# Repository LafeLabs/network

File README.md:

# [The Network](https://github.com/LafeLabs/network)

*everything replicates!*

 - [index.html](index.html)
 - [MUSIC/](music/)
 - [STONE SOUP/](stonesoup/)
 - [BRACKETS/](brackets/)
 - [TERMINAL/](terminal/)
 - [PODCASTS/](podcasts/)
 - [BOOKS/](books/)
 - [ZINES/](zines/)
 - [Fashion/](fashion/)
 - [Freestore/](freestore/)
 - [Laws of the Network/](laws/)
 - [DIRT PIPE/](dirtpipe/)
 - [INTERNET OF SQUARES/](squares/)
 - [write on the wall](wall.html)
 - [page/](page/)
 - [QR Code](qrcode.html)
 - [STREET NETWORK/](street/)
 - [WATERSHED NETWORK](watershed/)
 - [WHAT CAN I DO FOR THE NETWORK?/](network-actions/)
 - [WHAT CAN THE NETWORK DO FOR ME?](network-benefits/)
 - [fork.html](fork.html)

1. Get a 8 foot 1x4.
2. Cut off two sections each 24 inches long
3. Cut off a section 28 inches long
4. print out the screen bracket
5. print out the board bracket
6. print out 4 of the flat bracket
6. print out the pi bracket and add M2.5 thread inserts
7. print out the circuit playground bracket and add 4-40 thread inserts
8. drill all the holes in all the boards
9. assemble all the screws

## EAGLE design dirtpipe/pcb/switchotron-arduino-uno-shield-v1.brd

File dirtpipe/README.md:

## [Up A Level](../)

# [DIRT PIPE](https://github.com/LafeLabs/network/tree/main/dirtpipe)

## RITUAL THE FIRST

GET DIRT PIPE FROM A MAKER, TEST IT OUT, PLAY THE BUTTONS AND THE KNOBS

## RITUAL THE SECOND

INSTALL THE [ARDUINO IDE](https://www.arduino.cc/en/software)

INSTALL THE MOZZI LIBRARY

INSTALL THE ADAFRUIT NEOPIXEL LIBRARY

COPY/PASTE THE CODE FROM THE BOTTOM OF THIS DOCUMENT INTO THE ARDUINO IDE, BEING SURE TO TOTALLY REPLACE THE DEFAULT CODE RATHER THAN ADD TO IT

CHECK THE CODE BY CLICKING THE CHECK BOX

UPLOAD THE CODE

RE-TEST THE DIRT PIPE

## RITUAL THE THIRD

CHANGE THE DIRT PIPE TO PLAY A TONE AT SOME FIXED FREQUENCY

CHANGE THE COLORS OF THE BUTTONS

CREATE YOUR OWN THING AND SHARE IT WITH THE WORLD

[link to the circuit boards on pcbway.com](https://www.pcbway.com/project/shareproject/W224521BSI51_dirtpipe_UNO_shield_v1_2024_04_04_8aeaeaa8.html)

[digikey cart with all the parts other than headers](https://www.digikey.com/short/bcr3z21v)

[headers on amazon](https://www.amazon.com/Header-Lystaii-Pin-Connector-Electronic/dp/B06ZZN8L9S/)

## 1/2 inch #4 wood screws

## 4-40 Screws for Arduino UNO and Circuit Playground Express

## 4-40 Thread Inserts

## Thread insert tool 

## AnkerMake 3d printer

```
#include <Adafruit_NeoPixel.h>
#ifdef __AVR__
#endif

// Which pin on the Arduino is connected to the NeoPixels?
#define PIN 12 // On Trinket or Gemma, suggest changing this to 1

// How many NeoPixels are attached to the Arduino?
#define NUMPIXELS 8 // 
//there are 8

// When setting up the NeoPixel library, we tell it how many pixels,  
// and which pin to use to send signals. Note that for older NeoPixel
// strips you might need to change the third parameter -- see the
// strandtest example for more information on possible values.
Adafruit_NeoPixel pixels(NUMPIXELS, PIN, NEO_GRB + NEO_KHZ800);

int buttons0 = 0;
int buttons1 = 0;
int buttons0_2 = 0;
int buttons1_2 = 0;
int buttonmode0 = 0;
int buttonmode1 = 0;

int modevoltage1 = 110;
int modevoltage2 = 215;
int modevoltage3 = 320;
int modevoltage4 = 425;
int modevoltage5 = 542;
int modevoltage6 = 670;
int modevoltage7 = 820;

int delta =  20;

int knob = 0;
boolean on = false;
boolean test = false;

#include <MozziGuts.h>
#include <Oscil.h> // oscillator template
#include <tables/sin2048_int8.h> // sine table for oscillator

// use: Oscil <table_size, update_rate> oscilName (wavetable), look in .h file of table #included above
Oscil <SIN2048_NUM_CELLS, AUDIO_RATE> aSin(SIN2048_DATA);

// use #define for CONTROL_RATE, not a constant
#define CONTROL_RATE 64 // Hz, powers of 2 are most reliable

void setup() {
    Serial.begin(115200);
    knob = analogRead(A3);
    buttons0 = analogRead(A0);
    buttons1 = analogRead(A1);
    pinMode(15,INPUT_PULLUP);
    pinMode(16,INPUT_PULLUP);
    pixels.begin(); // INITIALIZE NeoPixel strip object (REQUIRED)
    startMozzi(CONTROL_RATE); // :)
    aSin.setFreq(2600); // set the freq to knob in Hz
    pinMode(9,OUTPUT); 

}
void updateControl(){
  // put changing controls in here
}

AudioOutput_t updateAudio(){
  return MonoOutput::from8Bit(aSin.next()); // return an int signal centred around 0
}

void loop() {

  buttons0 = analogRead(A0);
  buttons1 = analogRead(A4);
  //delay(30);
  buttons0_2 = analogRead(A0);
  buttons1_2 = analogRead(A4);

  knob = analogRead(A3);
  on = !digitalRead(15);
  test = !digitalRead(16);

  if(buttons0 <  delta && buttons0_2 < delta){
    buttonmode0 = 0;
  }
  if(buttons0 > modevoltage1 - delta && buttons0 < modevoltage1 + delta && buttons0_2 > modevoltage1 - delta && buttons0_2 < modevoltage1 + delta){
    buttonmode0 = 1;
  }
  if(buttons0 > modevoltage2 - delta && buttons0 < modevoltage2 + delta && buttons0_2 > modevoltage2 - delta && buttons0_2 < modevoltage2 + delta){
    buttonmode0 = 2;
  }
  if(buttons0 > modevoltage3 - delta && buttons0 < modevoltage3 + delta && buttons0_2 > modevoltage3 - delta && buttons0_2 < modevoltage3 + delta){
    buttonmode0 = 3;
  }
  if(buttons0 > modevoltage4 - delta && buttons0 < modevoltage4 + delta && buttons0_2 > modevoltage4 - delta && buttons0_2 < modevoltage4 + delta){
    buttonmode0 = 4;
  }
  if(buttons0 > modevoltage5 - delta && buttons0 < modevoltage5 + delta && buttons0_2 > modevoltage5 - delta && buttons0_2 < modevoltage5 + delta){
    buttonmode0 = 5;
  }
  if(buttons0 > modevoltage6 - delta && buttons0 < modevoltage6 + delta && buttons0_2 > modevoltage6 - delta && buttons0_2 < modevoltage6 + delta){
    buttonmode0 = 6;
  }
  if(buttons0 > modevoltage7 - delta && buttons0 < modevoltage7 + delta && buttons0_2 > modevoltage7 - delta && buttons0_2 < modevoltage7 + delta){
    buttonmode0 = 7;
  }
  if(buttons0 > 1024 - delta && buttons0_2 > 1024 - delta){
    buttonmode0 = 8;
  }

  if(buttons1 <  delta && buttons1_2 < delta){
    buttonmode1 = 0;
  }
  if(buttons1 > modevoltage1 - delta && buttons1 < modevoltage1 + delta && buttons1_2 > modevoltage1 - delta && buttons1_2 < modevoltage1 + delta){
    buttonmode1 = 1;
  }
  if(buttons1 > modevoltage2 - delta && buttons1 < modevoltage2 + delta && buttons1_2 > modevoltage2 - delta && buttons1_2 < modevoltage2 + delta){
    buttonmode1 = 2;
  }
  if(buttons1 > modevoltage3 - delta && buttons1 < modevoltage3 + delta && buttons1_2 > modevoltage3 - delta && buttons1_2 < modevoltage3 + delta){
    buttonmode1 = 3;
  }
  if(buttons1 > modevoltage4 - delta && buttons1 < modevoltage4 + delta && buttons1_2 > modevoltage4 - delta && buttons1_2 < modevoltage4 + delta){
    buttonmode1 = 4;
  }
  if(buttons1 > modevoltage5 - delta && buttons1 < modevoltage5 + delta && buttons1_2 > modevoltage5 - delta && buttons1_2 < modevoltage5 + delta){
    buttonmode1 = 5;
  }
  if(buttons1 > modevoltage6 - delta && buttons1 < modevoltage6 + delta && buttons1_2 > modevoltage6 - delta && buttons1_2 < modevoltage6 + delta){
    buttonmode1 = 6;
  }
  if(buttons1 > modevoltage7 - delta && buttons1 < modevoltage7 + delta && buttons1_2 > modevoltage7 - delta && buttons1_2 < modevoltage7 + delta){
    buttonmode1 = 7;
  }
  if(buttons1 > 1024 - delta && buttons1_2 > 1024 - delta){
    buttonmode1 = 8;
  }

   if(buttonmode0 == 0 && buttonmode1 == 0){
    pixels.setPixelColor(0, pixels.Color(0, 0, 0));    
    pixels.setPixelColor(1, pixels.Color(0, 0, 0));    
    pixels.setPixelColor(2, pixels.Color(0, 0, 0));    
    pixels.setPixelColor(3, pixels.Color(0, 0, 0));    
    pixels.setPixelColor(4, pixels.Color(0, 0, 0));    
    pixels.setPixelColor(5, pixels.Color(0, 0, 0));    
    pixels.setPixelColor(6, pixels.Color(0, 0, 0));    
    pixels.setPixelColor(7, pixels.Color(0, 0, 0));     
   }
   if(buttonmode0 !=0 && buttonmode0 == buttonmode1){
    pixels.setPixelColor(0, pixels.Color(0, 0, 0));    
    pixels.setPixelColor(1, pixels.Color(0, 0, 0));    
    pixels.setPixelColor(2, pixels.Color(0, 0, 0));    
    pixels.setPixelColor(3, pixels.Color(0, 0, 0));    
    pixels.setPixelColor(4, pixels.Color(0, 0, 0));    
    pixels.setPixelColor(5, pixels.Color(0, 0, 0));    
    pixels.setPixelColor(6, pixels.Color(0, 0, 0));    
    pixels.setPixelColor(7, pixels.Color(0, 0, 0));     
    pixels.setPixelColor(buttonmode0 - 1, pixels.Color(200, 0, 200));        //purple
   }
   if(buttonmode0 !=0 && buttonmode0 != buttonmode1){
    pixels.setPixelColor(0, pixels.Color(0, 0, 0));    
    pixels.setPixelColor(1, pixels.Color(0, 0, 0));    
    pixels.setPixelColor(2, pixels.Color(0, 0, 0));    
    pixels.setPixelColor(3, pixels.Color(0, 0, 0));    
    pixels.setPixelColor(4, pixels.Color(0, 0, 0));    
    pixels.setPixelColor(5, pixels.Color(0, 0, 0));    
    pixels.setPixelColor(6, pixels.Color(0, 0, 0));    
    pixels.setPixelColor(7, pixels.Color(0, 0, 0));     
    pixels.setPixelColor(buttonmode0 - 1, pixels.Color(200, 0,0));        //red
    pixels.setPixelColor(buttonmode1 - 1, pixels.Color(0, 0,200));        //blue

   }
   if(buttonmode0 !=0 && buttonmode1 == 0){
    pixels.setPixelColor(0, pixels.Color(0, 0, 0));    
    pixels.setPixelColor(1, pixels.Color(0, 0, 0));    
    pixels.setPixelColor(2, pixels.Color(0, 0, 0));    
    pixels.setPixelColor(3, pixels.Color(0, 0, 0));    
    pixels.setPixelColor(4, pixels.Color(0, 0, 0));    
    pixels.setPixelColor(5, pixels.Color(0, 0, 0));    
    pixels.setPixelColor(6, pixels.Color(0, 0, 0));    
    pixels.setPixelColor(7, pixels.Color(0, 0, 0));     
    pixels.setPixelColor(buttonmode0 - 1, pixels.Color(200, 0,0));        //red

   }

   if(buttonmode1 !=0 && buttonmode0 == 0){
    pixels.setPixelColor(0, pixels.Color(0, 0, 0));    
    pixels.setPixelColor(1, pixels.Color(0, 0, 0));    
    pixels.setPixelColor(2, pixels.Color(0, 0, 0));    
    pixels.setPixelColor(3, pixels.Color(0, 0, 0));    
    pixels.setPixelColor(4, pixels.Color(0, 0, 0));    
    pixels.setPixelColor(5, pixels.Color(0, 0, 0));    
    pixels.setPixelColor(6, pixels.Color(0, 0, 0));    
    pixels.setPixelColor(7, pixels.Color(0, 0, 0));     
    pixels.setPixelColor(buttonmode1 - 1, pixels.Color(0, 0,200));        //blue

   }

  pixels.show();   // Send the updated pixel colors to the hardware.

  aSin.setFreq((buttonmode0+1)*knob);      

/*
  if(on){
  }
  if(!on && !test){
    aSin.setFreq(0);      

  }

*/

audioHook(); // required here

//Serial.println(buttons0);

//Serial.println(buttonmode1);

/*  
  Serial.print(buttons0); 
  Serial.print(",");   
  Serial.print(buttons1); 
  Serial.print(",");   
  Serial.println(knob); 

  if(on){
    Serial.println("ON");
  }
  if(test){
    Serial.println("TEST");
  }
  if(!on && !test){
    Serial.println("OFF");
  }
*/
  
}
```

## DIRT PIPE REPLICATOR CODE:

```
sudo wget https://raw.githubusercontent.com/LafeLabs/network/main/dirtpipe/replicator.sh -O replicator.sh
sudo sh replicator.sh
```

## LINKS

 - [editor.php](editor.php)
 - [webeditor.html](webeditor.html)
 - [localhost](http://localhost)
 - [write on the wall](wall.html)
 - [DIRT WIZARD ON TIKTOK](https://www.tiktok.com/@dirt_wizard666)
 - [DIRT WIZARD ON CYBERPUNK.LOL](https://cyberpunk.lol/@dirtwizard)
 - [DIRT WIZARD ON SHARKEY](https://shark.distantserver.org/@dirtwizard)
 - [DIRT WIZARD ON GITHUB](https://github.com/lafeLabs/)
 - [QR Code](qrcode.html)
 - [fork.html](fork.html)

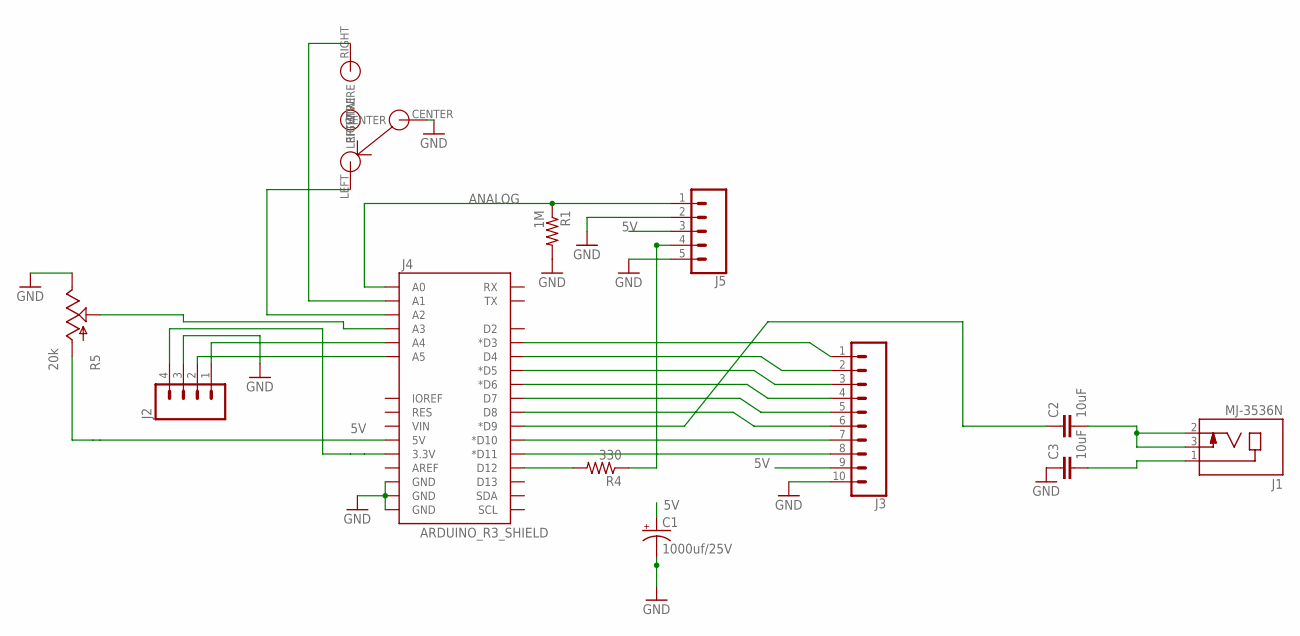
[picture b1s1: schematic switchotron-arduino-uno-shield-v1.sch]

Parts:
C1: 1000uf/25V; CPOL-RADIAL-1000UF-25V-KIT
C2, C3: 10uF; 0805
J1: MJ-3536N; CUI_MJ-3536N
J2: M04PTH; 1X04
J3: CONN_10"; 1X10
J4: ARDUINO_R3_SHIELD; UNO_R3_SHIELD
J5: CONN_05; 1X05
R1: 1M; R0603
R4: 330; R0603
R5: 20k; ALPS_POT_KIT
SW3: ON-OFF-ON-360-1013-ND; 360-1013-ND

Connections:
5V: C1.+, J3.9, J4.5V, J5.3, R5.P$3 (A)
ANALOG: J4.A0, J5.1, R1.1
BUTTON: J4.A1, SW3.RIGHT (RIGHTWIRE)
CL: J2.2, J4.A5
DA: J2.1, J4.A4
GND: C1.-, C3.1, J2.3, J3.10, J4.GND@0 (GND), J4.GND@1 (GND), J4.GND@2 (GND), J5.2, J5.5, R1.2, R5.P$1 (E), SW3.CENTER
unnamed: J4.D12, R4.2
unnamed: J4.A3, R5.P$2 (S)
unnamed: J3.8, J4.D11 (*D11)
unnamed: J3.7, J4.D10 (*D10)
unnamed: J3.6, J4.D8
unnamed: J3.5, J4.D7
unnamed: J3.4, J4.D6 (*D6)
unnamed: J3.3, J4.D5 (*D5)
unnamed: J3.2, J4.D4
unnamed: J4.A2, SW3.LEFT (LEFTWIRE)
unnamed: J3.1, J4.D3 (*D3)
unnamed: C3.2, J1.1
unnamed: C2.2, J1.2, J1.3
unnamed: C2.1, J4.D9 (*D9)
unnamed: J5.4, R4.1
VCC: J2.4, J4.3.3V

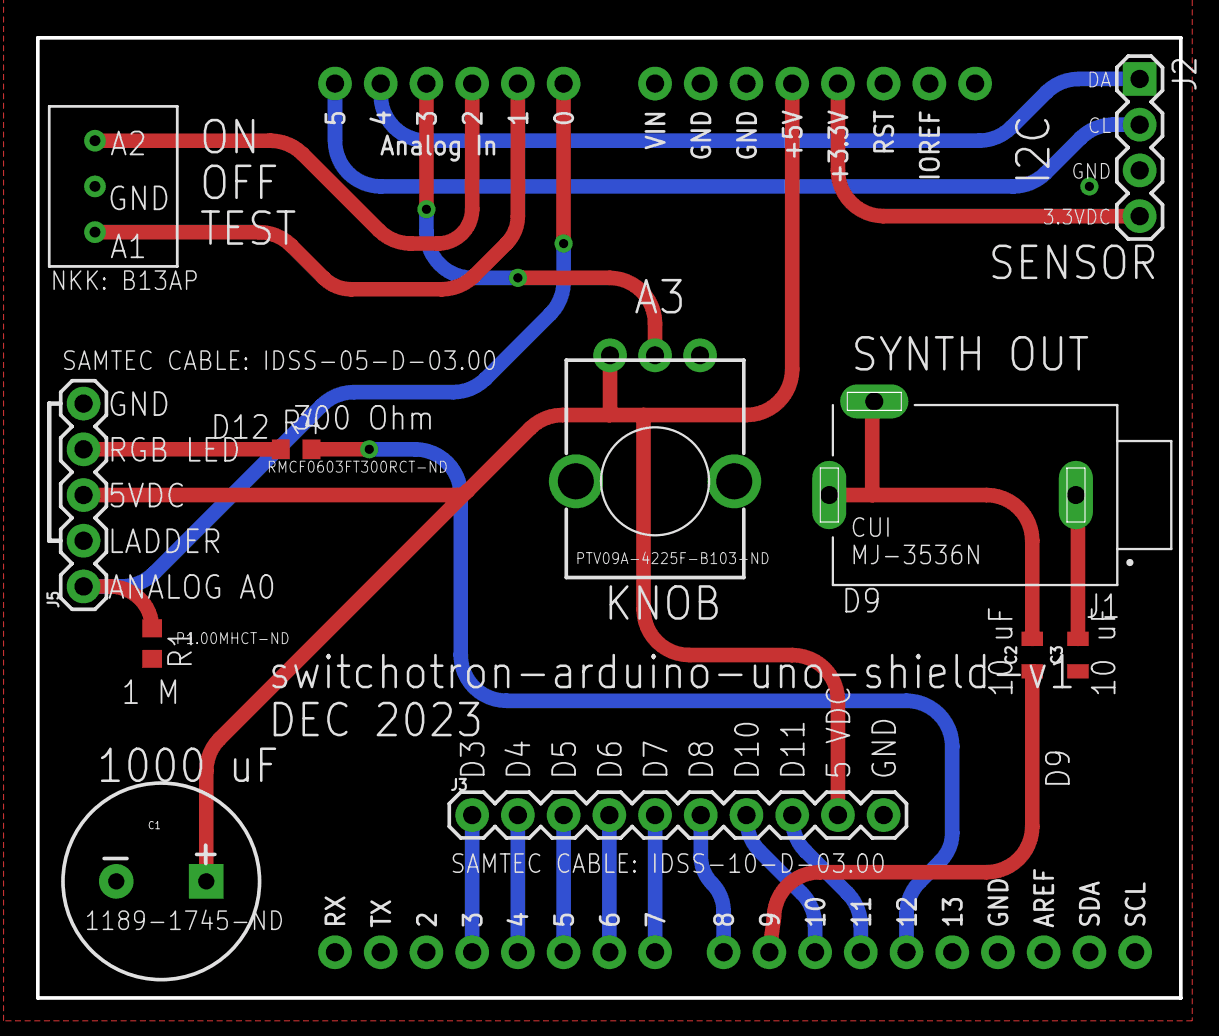
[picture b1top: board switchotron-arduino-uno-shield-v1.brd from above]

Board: 2 copper layers, 63.5 x 53.3 mm, 12 parts (0 on the bottom side), 22 nets.

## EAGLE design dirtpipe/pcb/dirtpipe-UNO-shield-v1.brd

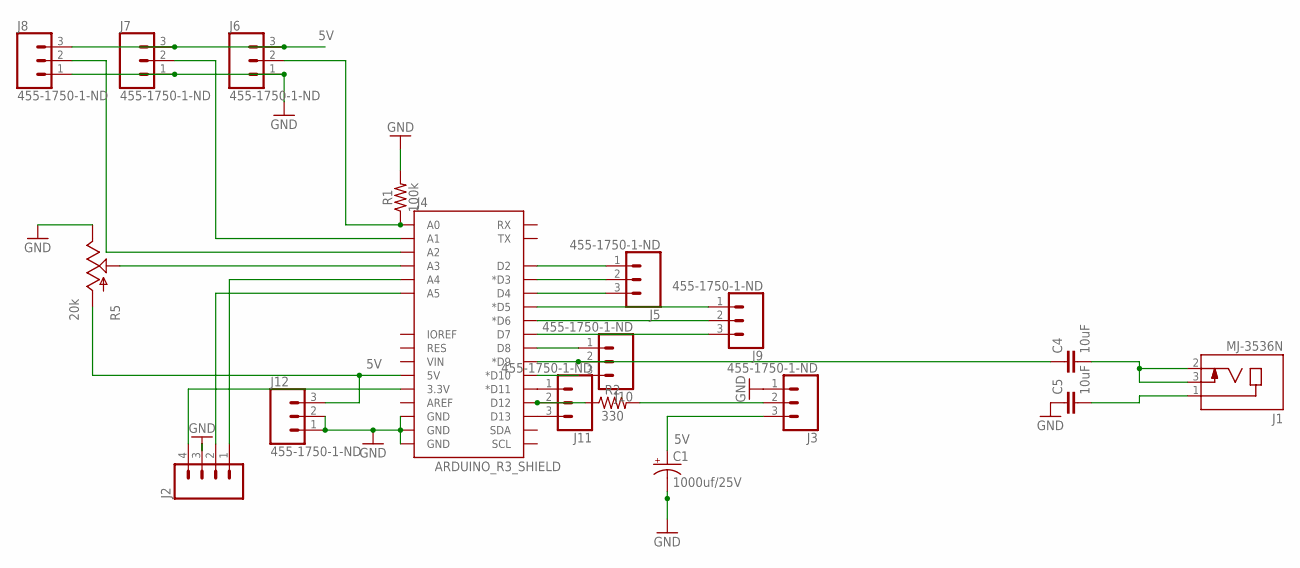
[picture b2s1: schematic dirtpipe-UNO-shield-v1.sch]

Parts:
C1: 1000uf/25V; CPOL-RADIAL-1000UF-25V-KIT
C4, C5: 10uF; CAP-PTH-SMALL-KIT
J1: MJ-3536N; CUI_MJ-3536N
J2: M04PTH; 1X04
J3, J5, J6, J7, J8, J9, J10, J11, J12: 455-1750-1-ND; 1X03
J4: ARDUINO_R3_SHIELD; UNO_R3_SHIELD
R1: 100k; AXIAL-0.3
R2: 330; AXIAL-0.3
R5: 20k; ALPS_POT_KIT

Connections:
5V: C1.+, J3.3, J4.5V, J6.3, J7.3, J8.3, J12.3, R5.P$3 (A)
CL: J2.2, J4.A5
DA: J2.1, J4.A4
GND: C1.-, C5.1, J2.3, J3.1, J4.GND@0 (GND), J4.GND@1 (GND), J4.GND@2 (GND), J6.1, J7.1, J8.1, J12.1, J12.2, R1.P$2 (2), R5.P$1 (E)
unnamed: J4.D12, J11.2, R2.P$1 (1)
unnamed: J4.A3, R5.P$2 (S)
unnamed: J4.D2, J5.1
unnamed: J4.D3 (*D3), J5.2
unnamed: J4.D4, J5.3
unnamed: J4.D5 (*D5), J9.1
unnamed: J4.D6 (*D6), J9.2
unnamed: J4.D7, J9.3
unnamed: J4.D8, J10.1
unnamed: J4.D10 (*D10), J10.3
unnamed: J4.D11 (*D11), J11.1
unnamed: C5.2, J1.1
unnamed: C4.2, J1.2, J1.3
unnamed: C4.1, J4.D9 (*D9), J10.2
unnamed: J3.2, R2.P$2 (2)
unnamed: J4.A0, J6.2, R1.P$1 (1)
unnamed: J4.A1, J7.2
unnamed: J4.A2, J8.2
unnamed: J4.D13, J11.3
VCC: J2.4, J4.3.3V

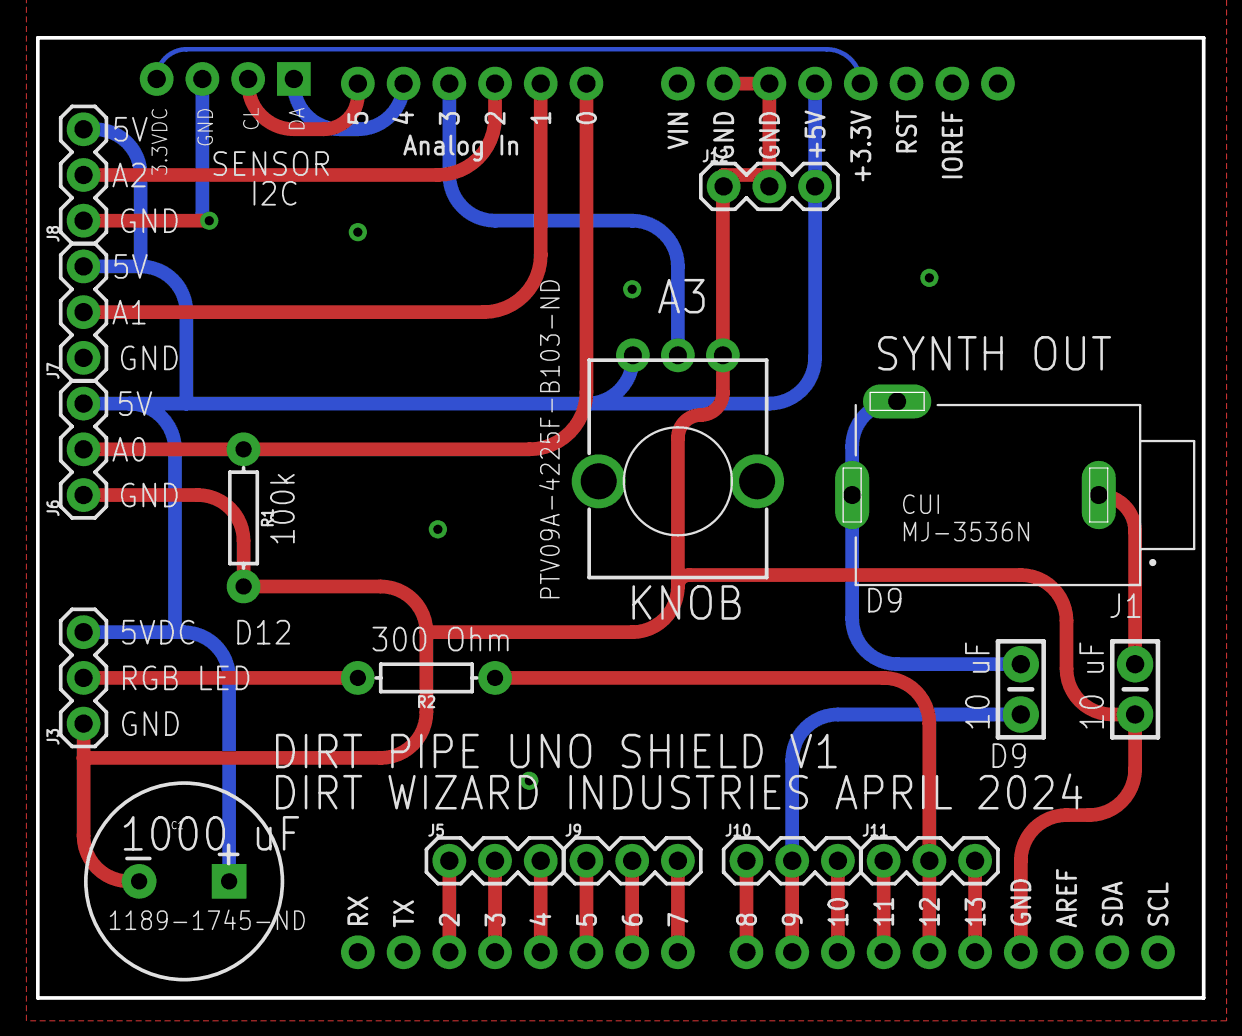
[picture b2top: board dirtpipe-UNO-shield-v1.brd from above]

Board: 2 copper layers, 64.8 x 53.3 mm, 18 parts (1 on the bottom side), 24 nets.

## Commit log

2023-08-06 the network begins in earnest now
2023-08-06 made it like community rather than trashfeed
2023-08-06 added light/dark mode button functionality to webeditor.html
2023-08-07 building out the whole structure of the network
2023-08-07 adding lots of random things to the set!
2023-08-07 more random changes
2023-08-07 putting together the pieces of the set
2023-08-07 making more products
2023-08-07 rulers
2023-08-07 platonic solids and quantum dump
2023-08-07 PLATONIC SOLIDS!
2023-08-07 MADNESS! TOTAL RECURSION!
2023-08-07 a few more updates to the sets
2023-08-07 a bunchof updates
2023-08-07 skeletron and trash tie trash magic replicator images
2023-08-07 hypersign is in the set of products now
2023-08-07 making more pages
2023-08-08 a-human.html is the prototype for making a new page, added screen shots of process
2023-08-08 trash magic replication
2023-08-08 more web replication
2023-08-08 make a page is in the loop for full recursion
2023-08-08 made a minimal fork just to see what it's like, made little improvements to the page about making pages
2023-08-10 sloanslake up and goog image gone
2023-08-10 more images from the lake
2023-08-12 trash board!!!
2023-08-12 trash robot dot org replciation
2023-08-12 trash boards updates
2023-08-15 backup whole system to a subdirectory so main can be stripped down to minimal again
2023-08-15 total reorg, this is now very stripped down trash magic, with still more clarification to go
2023-08-15 making the readme a proper replicator
2023-08-15 removed unused files again
2023-08-15 small changes, removed bad qrcode image
2023-08-15 this thing is so close to ready to unleash on the world...
2023-08-15 cleaning up link structure
2024-03-27 something is badly wrong
2024-03-27 cloned "cart"
2024-03-27 music in the network
2024-03-27 music copied
2024-03-27 replicators
2024-03-27 change name of copy script
2024-03-27 added images to an album
2024-03-27 music
2024-03-28 making the replicators fully recursive one by one
2024-03-28 fixing replicators more
2024-03-28 one more album fully recursive
2024-03-28 all 6 albums now have full replicator.php recursion
2024-03-28 top level replicator is recursive now for discography
2024-03-28 one missing full recursion conversion on replicator set
2024-03-29 replication sets
2024-03-30 changed names of folders to "tracks" and "images" rather than "mixtape" and "trashmagic"
2024-03-30 readme updates
2024-03-30 TOTAL RECURSION
2024-03-30 REPLICATION!
2024-03-30 update core set
2024-03-30 added the wall to the set
2024-03-30 sensor code
2024-03-30 album prototype
2024-03-30 more recursion
2024-03-31 album recursion amplification
2024-03-31 total replication
2024-03-31 even more recursion-y
2024-03-31 building structure
2024-03-31 more replication
2024-03-31 making all the albums into the same prototype
2024-03-31 qr code replicators
2024-03-31 fixed code to grab correct folder of songs
2024-03-31 fixing the things
2024-03-31 put singles album in proper configuration
2024-03-31 more spores
2024-03-31 another replicator done
2024-03-31 this might be all of it, just about for the discography
2024-03-31 replicating the set of self-replicating sets which is "discography"
2024-03-31 using -O in each replicator script to write over existing files
2024-03-31 making a minimal self-replicating web page as a prototype
2024-03-31 make page more universal
2024-03-31 page recursion
2024-03-31 brackets is a thing
2024-03-31 SELF REPLICATING BRACKETS
2024-03-31 circuit playground express code
2024-03-31 the brackets are close to a fully magic set
2024-03-31 update replicator scrolls, so .STL is with caps to fix case problem in file urls on servers
2024-03-31 dirtpipe
2024-04-01 making my books into a set
2024-04-02 dirt pipe!
2024-04-03 books replicators
2024-04-04 putting the dirt pipe circuits together
2024-04-04 I AM A SELF REPLICATING LIBRARY OF SELF-REPLICATING BOOKS!
2024-04-04 fixed a misspelling in the replicator
2024-04-06 many things are replicating, as many as we can
2024-04-06 terminal replicators
2024-04-07 dirt pipe is closer to being functional as a set
2024-04-08 i am the replicator we are the replicators
2024-04-08 the cubes of dirt are replicating across the land
2024-04-08 dirt pipe qr code
2024-04-10 THE NETWORK OF THE STREET,
2024-04-10 MORE UPDATES ON NETWORK ONTOLOGY
2024-04-10 WHAT CAN THE NETWORK DO FOR ME?
2024-04-11 my god, microsoft, can you break things any more? THis will be my last microsoft computer.
2024-04-12 quantum art is part of the network
2024-04-12 quantum art becomes fully recursive
2024-04-12 what is happening? who knows?
2024-04-13 THE DOOMGAZER GENERAL JOINS THE NETWORK
2024-04-13 replicate the repilcators
2024-04-14 replicating the flags, 3d print files for terminal
2024-04-16 stone soup
2024-04-16 qr codes in the soup
2024-04-16 stone soup is just about ready to cook
2024-04-16 update readme and dna
2024-04-16 increase of recursion
2024-04-16 stone soup is really just about a thing now
2024-04-17 stone soup work
2024-04-20 many things which replicate are replicated
2024-04-22 made top level of network its own page, like colfax.site
2024-04-22 qrcodes
2024-04-23 replicating the core set of the network terminal as main part of network
2024-04-24 adding non-amazon parts to bill of materials
2024-04-24 adding elements to the core network constructor set
2024-04-25 gutenberg library clone

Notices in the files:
parts and their libraries:
SparkFun-Boards: Licensing: Creative Commons ShareAlike 4.0 International - https://creativecommons.org/licenses/by-sa/4.0
